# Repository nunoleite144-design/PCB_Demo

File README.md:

# PCB do Painel Solar 1U — ICARUS

Repositório de trabalho relativo ao desenho preliminar da PCB do painel solar 1U do projeto ICARUS, no âmbito da Porto Space Team.

Esta versão agrega o projeto KiCad, os footprints preliminares e a documentação técnica de apoio à revisão interna.

## Revisão atual

A revisão de trabalho actual é a **v0.7**:

- `hardware/ICARUS_1U_Solar_Panel_PCB_v0p7.kicad_sch`
- `hardware/ICARUS_1U_Solar_Panel_PCB_v0p7.kicad_pcb`
- `hardware/ICARUS_1U_Solar_Panel_PCB_v0p7.kicad_pro`

Esta revisão adopta **1S2P (duas células em paralelo)** como topologia base, **move o conector Molex `J1` para a face inferior (`B.Cu`)** conforme orientação do líder de equipa, mantém os test pads `PANEL_NEG` e `PANEL_POS`, e mantém `BENCH_ONLY_PANEL_NEG`/`BENCH_ONLY_PANEL_POS` apenas como fallback de bancada. O `D1` (TVS DNP) e o `TP2` (SERIES_MID) da v0.6 foram **removidos** porque deixam de ser necessários em paralelo.

Estado desta revisão: **pré-validação física**. Não está aprovada para fabrico final nem para voo.

A v0.6 (2S1P série) permanece em histórico Git como branch `v0.6-internal-review` e em `main` antes do merge da v0.7.

## Estado atual

A configuração elétrica de referência é **1S2P** com duas células solares **TJ3xSCA-4080 Tipo 32** por painel, ligadas em paralelo.

Parâmetros de referência usados no dimensionamento:

| Parâmetro | Valor |
|---|---:|
| `Voc_cell` | 2.70 V @ 25 °C |
| `Vmp_cell` | 2.37 V @ 25 °C |
| `Jm` | 17.9 mA/cm² |
| Área ativa | 30.18 cm² |
| `dVoc/dT` | −6.0 mV/°C por célula |

Valores calculados para o painel 1S2P:

| Grandeza | Valor |
|---|---:|
| `Voc_panel` @ 25 °C BOL | 2.70 V |
| `Vmp_panel` @ 25 °C | 2.37 V |
| `Isc` @ 25 °C | ≈ 1.12 A |
| `Imp` @ 25 °C | ≈ 1.08 A |
| `Pmp` @ 25 °C | ≈ 2.65 W |

Ligação elétrica final (1S2P):

| Nó | Ligação |
|---|---|
| `SC1_NEG` (tabs/frente) | `PANEL_NEG` |
| `SC1_POS` (centro/verso) | `PANEL_POS` |
| `SC2_NEG` (tabs/frente) | `PANEL_NEG` |
| `SC2_POS` (centro/verso) | `PANEL_POS` |

Não existe net intermédia (`SERIES_MID` foi removida na transição 2S1P → 1S2P).

## Interface EPS I

O EPS usado é o **EnduroSat EPS I**. O pinout solar que deve ser respeitado no cabo/PCB é (Tabela 8 do EPS I User Manual):

| Pino do conector solar EPS I | Função |
|---:|---|
| 1 | PV− / negativo |
| 2 | PV− / negativo |
| 3 | PV+ / positivo |
| 4 | PV+ / positivo |

`J1` está montado em `B.Cu` (parte inferior da PCB) por instrução do líder de equipa, mantendo o pinout acima.

Limites relevantes por canal solar (Tabela 12 do EPS I User Manual):

| Limite | Valor | Notas |
|---|---:|---|
| Tensão mínima de entrada (boost UVLO) | ≈ 0.78 V | `VF_blocking_diode + 0.5 V` |
| Tensão típica de operação | 4.66 V | Ponto referenciado pelo EPS |
| Tensão máxima — OVP trigger | 5.5 V | EPS tem OVP **integrada** acima deste valor |
| Corrente máxima de entrada | 1.8 A | — |

A PCB e o harness devem ser verificados por continuidade antes de qualquer ligação ao EPS.

## Margens eléctricas (1S2P)

A transição para paralelo **elimina** o risco de sobretensão a frio que dominava a v0.6:

| Cenário | Valor 1S2P | vs limite 5.5 V (OVP trigger) |
|---|---:|---|
| `Voc_panel` @ 25 °C BOL | 2.70 V | margem 2.80 V |
| `Voc_panel` @ −40 °C BOL | 2.94 V | margem 2.56 V |
| `Voc_panel` @ −80 °C BOL (extremo) | 3.33 V | margem 2.17 V |

`Vmp` opera abaixo do ponto típico do EPS (2.37 V vs 4.66 V); o boost MPPT trabalha com rácio mais alto, com ligeira perda de eficiência mas funcionalmente correcto. UVLO ≈ 0.78 V está confortavelmente abaixo de `Vmp`.

Ver `docs/VALIDACAO_TOPOLOGIA_PARALELO_v0p7.md` para a análise completa.

## Conteúdo do repositório

- `hardware/` — projeto KiCad da PCB (esquemático, PCB, projeto), símbolos `ICARUS.kicad_sym`, footprints (`footprints/ICARUS_Solar.pretty`, `footprints/ICARUS_Connector.pretty`) e tabelas de bibliotecas.
- `docs/VALIDACAO_TOPOLOGIA_PARALELO_v0p7.md` — **documento de referência da v0.7**: justificação técnica, mapa de pads, mudanças aplicadas, estado dos relatórios.
- `docs/VALIDACAO_DATASHEETS_v0p6.md` — cruzamento do design com os datasheets oficiais (célula e EPS I); inclui actualização v0.7 sobre a OVP integrada.
- `docs/ANALISE_TERMICA_VOC_v0p6.md` — análise térmica de sobretensão (histórica, **superseded** pela mudança para 1S2P).
- `docs/DECISAO_TVS_v0p7.md` — decisão de clamp TVS (histórica, **superseded** — `D1` foi removido).
- `docs/CORRECAO_TOPOLOGIA_SERIE_v0p6.md` — correcção da anti-série da v0.6 (histórica).
- `docs/REVIEW_ACTIONS_v0p6.md` — resumo das ações da v0.6 (histórico).
- `docs/VALIDACAO_LOCAL_v0p6.md` — estado dos relatórios ERC/DRC da v0.6 (histórico).
- `docs/MECHANICAL_CELL_CLEARANCE_v0p6.md` — folga mecânica nominal entre células (continua válido em v0.7).
- `docs/CELL_UNDER_COPPER_RISK_v0p6.md` — auditoria de cobre sob as células da v0.6 (histórico parcial).
- `reports/` — relatórios ERC/DRC e plots SVG (top/bottom/fab) das revisões v0.6 e v0.7.
- `test_logs/LIBRARY_WARNINGS_WAIVER_v0p6.md` — waiver técnico dos warnings de biblioteca do ERC/DRC.
- `TJ30SCA-4080V4.pdf` — datasheet da célula solar TJ3xSCA-4080.
- `EPS_I_User_Manual.pdf` — manual do EnduroSat EPS I (limites de entrada solar e pinout do conector).

## Regra de fecho

Não considerar o desenho **flight-ready** nem **fabrication-ready** sem:

- ERC/DRC oficial no KiCad GUI (CLI já corrido e limpo);
- desenho de montagem CIC da AzurSpace (geometria das tabs e contacto de verso);
- drawing oficial do Molex 53398-0471 para validar footprint final;
- validação mecânica com estrutura e células reais;
- validação do harness por continuidade;
- testes elétricos com carga antes de ligação ao EPS;
- revisão por pelo menos uma segunda pessoa.

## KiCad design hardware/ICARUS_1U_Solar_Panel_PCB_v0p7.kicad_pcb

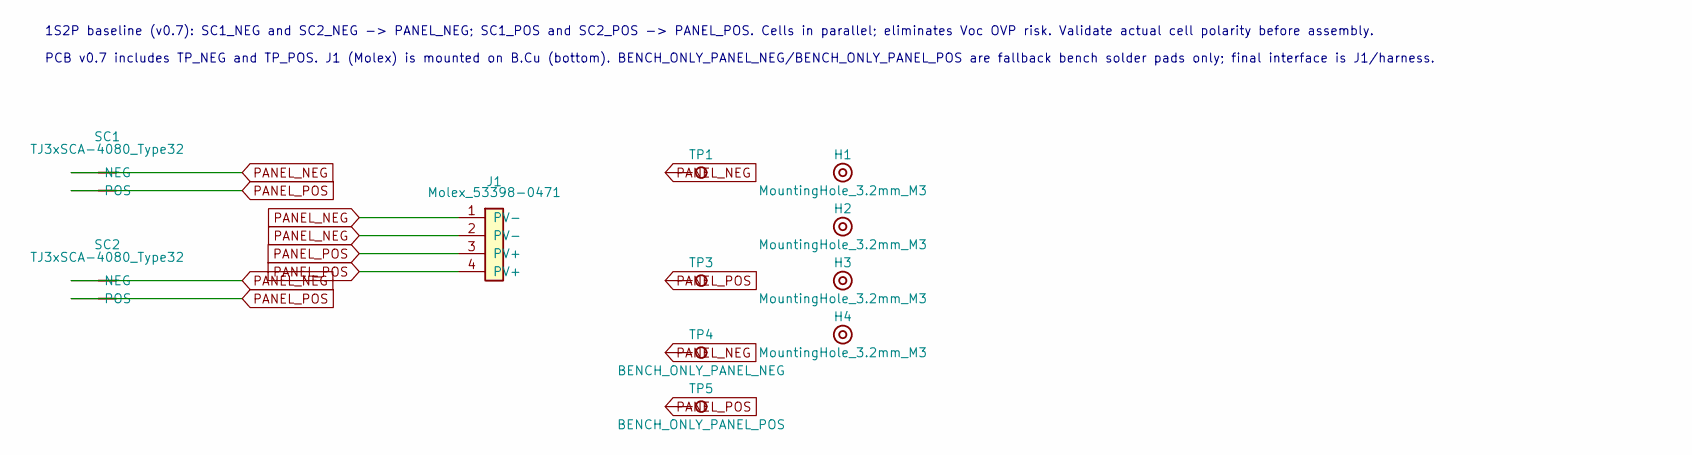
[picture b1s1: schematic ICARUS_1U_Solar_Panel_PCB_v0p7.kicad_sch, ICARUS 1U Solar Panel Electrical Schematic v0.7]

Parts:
H1, H2, H3, H4: MountingHole_3.2mm_M3
J1: Molex_53398-0471; Molex_53398-0471_1x04_P1.25mm_PRELIMINARY
SC1, SC2: TJ3xSCA-4080_Type32; TJ3xSCA_4080_CIC
TP1: PANEL_NEG; TestPoint_Pad_D2.0mm
TP3: PANEL_POS; TestPoint_Pad_D2.0mm
TP4: BENCH_ONLY_PANEL_NEG; TestPoint_Pad_D2.5mm
TP5: BENCH_ONLY_PANEL_POS; TestPoint_Pad_D2.5mm

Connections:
PANEL_NEG: J1.1 (PV-), J1.2 (PV-), SC1.1 (NEG), SC2.1 (NEG), TP1.1, TP4.1
PANEL_POS: J1.3 (PV+), J1.4 (PV+), SC1.2 (POS), SC2.2 (POS), TP3.1, TP5.1

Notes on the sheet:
1S2P baseline (v0.7): SC1_NEG and SC2_NEG -> PANEL_NEG; SC1_POS and SC2_POS -> PANEL_POS. Cells in parallel; eliminates Voc OVP risk. Validate actual cell polarity before assembly.
PCB v0.7 includes TP_NEG and TP_POS. J1 (Molex) is mounted on B.Cu (bottom). BENCH_ONLY_PANEL_NEG/BENCH_ONLY_PANEL_POS are fallback bench solder pads only; final interface is J1/harness.

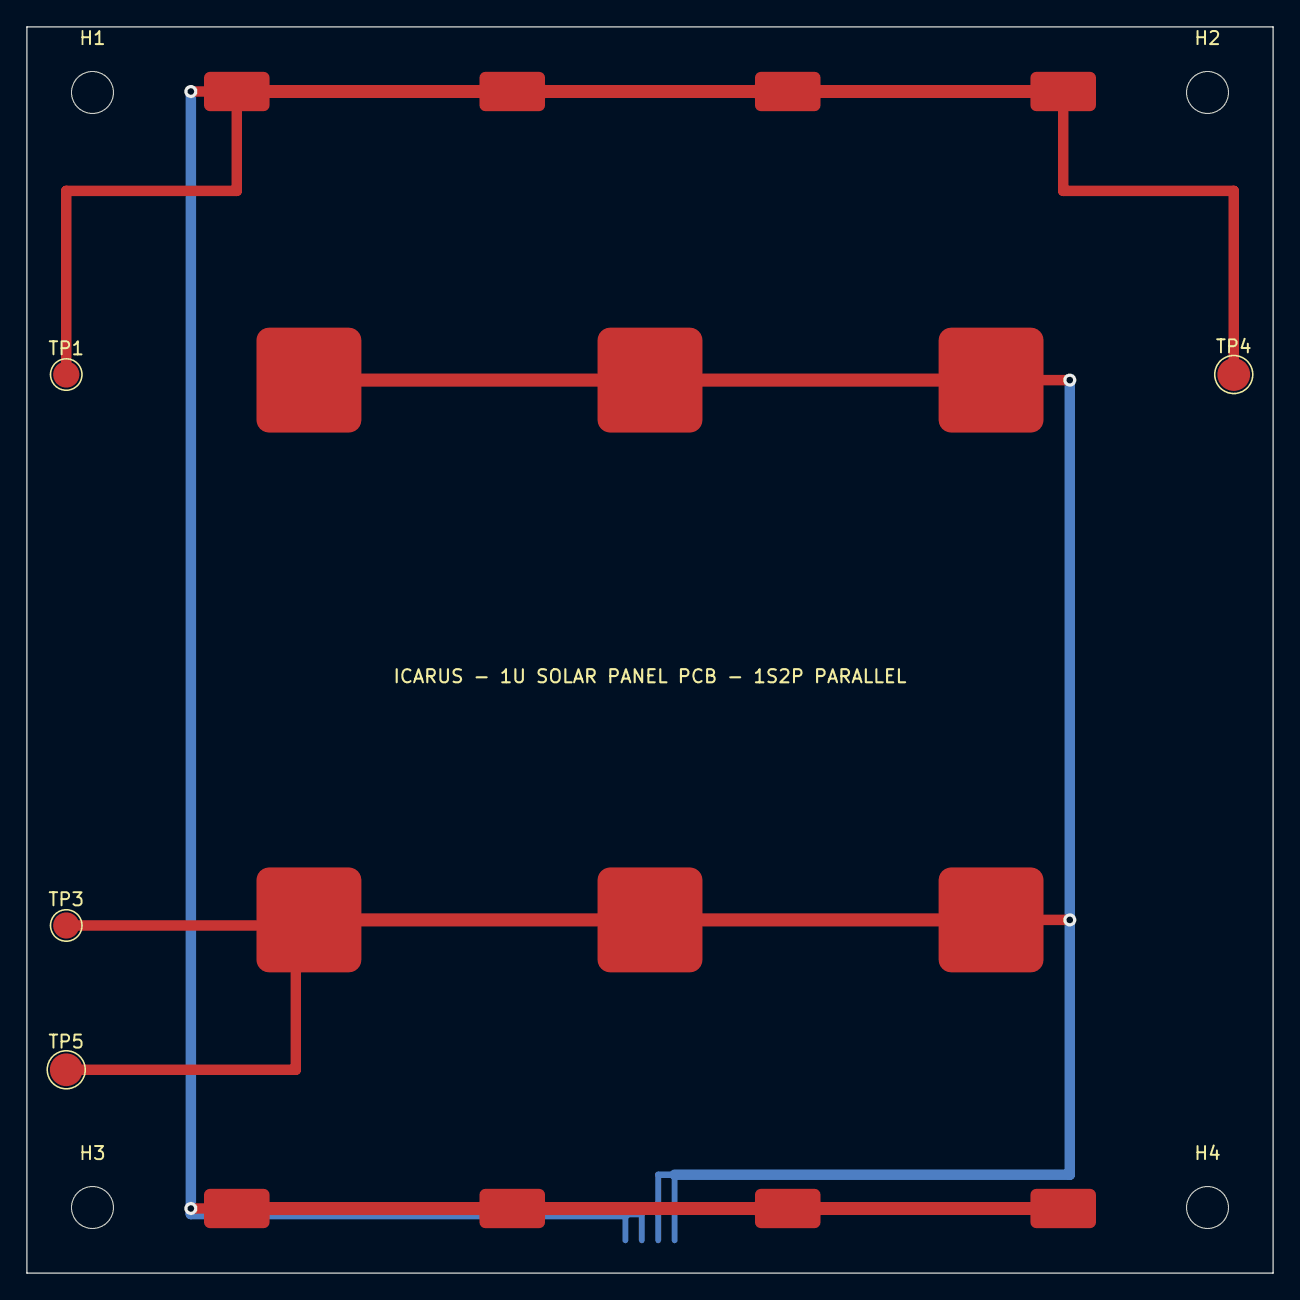
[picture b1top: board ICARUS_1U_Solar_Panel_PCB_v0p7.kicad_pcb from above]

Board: 2 copper layers, 95.0 x 95.0 mm, 11 parts (1 on the bottom side), 2 nets.

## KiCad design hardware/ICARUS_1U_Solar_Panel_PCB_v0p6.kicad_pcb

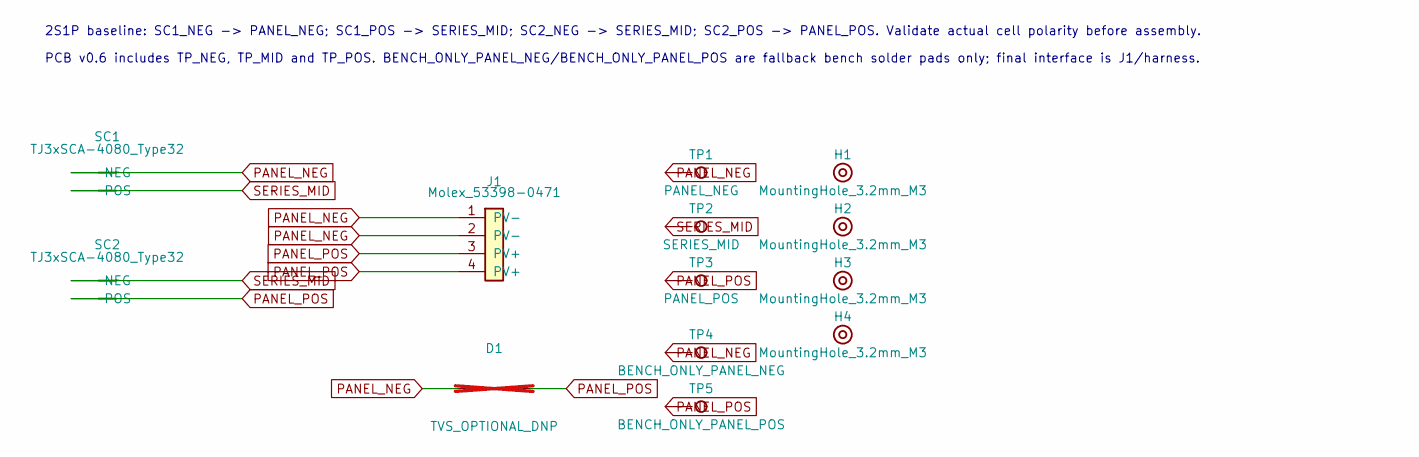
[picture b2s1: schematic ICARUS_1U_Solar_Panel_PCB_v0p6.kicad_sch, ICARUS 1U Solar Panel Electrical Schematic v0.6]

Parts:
D1: TVS_OPTIONAL_DNP; D_SOD-123; not fitted
H1, H2, H3, H4: MountingHole_3.2mm_M3
J1: Molex_53398-0471; Molex_53398-0471_1x04_P1.25mm_PRELIMINARY
SC1, SC2: TJ3xSCA-4080_Type32; TJ3xSCA_4080_CIC
TP1: PANEL_NEG; TestPoint_Pad_D2.0mm
TP2: SERIES_MID; TestPoint_Pad_D2.0mm
TP3: PANEL_POS; TestPoint_Pad_D2.0mm
TP4: BENCH_ONLY_PANEL_NEG; TestPoint_Pad_D2.5mm
TP5: BENCH_ONLY_PANEL_POS; TestPoint_Pad_D2.5mm

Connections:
PANEL_NEG: D1.1 (A), J1.1 (PV-), J1.2 (PV-), SC1.1 (NEG), TP1.1, TP4.1
PANEL_POS: D1.2 (K), J1.3 (PV+), J1.4 (PV+), SC2.2 (POS), TP3.1, TP5.1
SERIES_MID: SC1.2 (POS), SC2.1 (NEG), TP2.1

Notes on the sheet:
2S1P baseline: SC1_NEG -> PANEL_NEG; SC1_POS -> SERIES_MID; SC2_NEG -> SERIES_MID; SC2_POS -> PANEL_POS. Validate actual cell polarity before assembly.
PCB v0.6 includes TP_NEG, TP_MID and TP_POS. BENCH_ONLY_PANEL_NEG/BENCH_ONLY_PANEL_POS are fallback bench solder pads only; final interface is J1/harness.

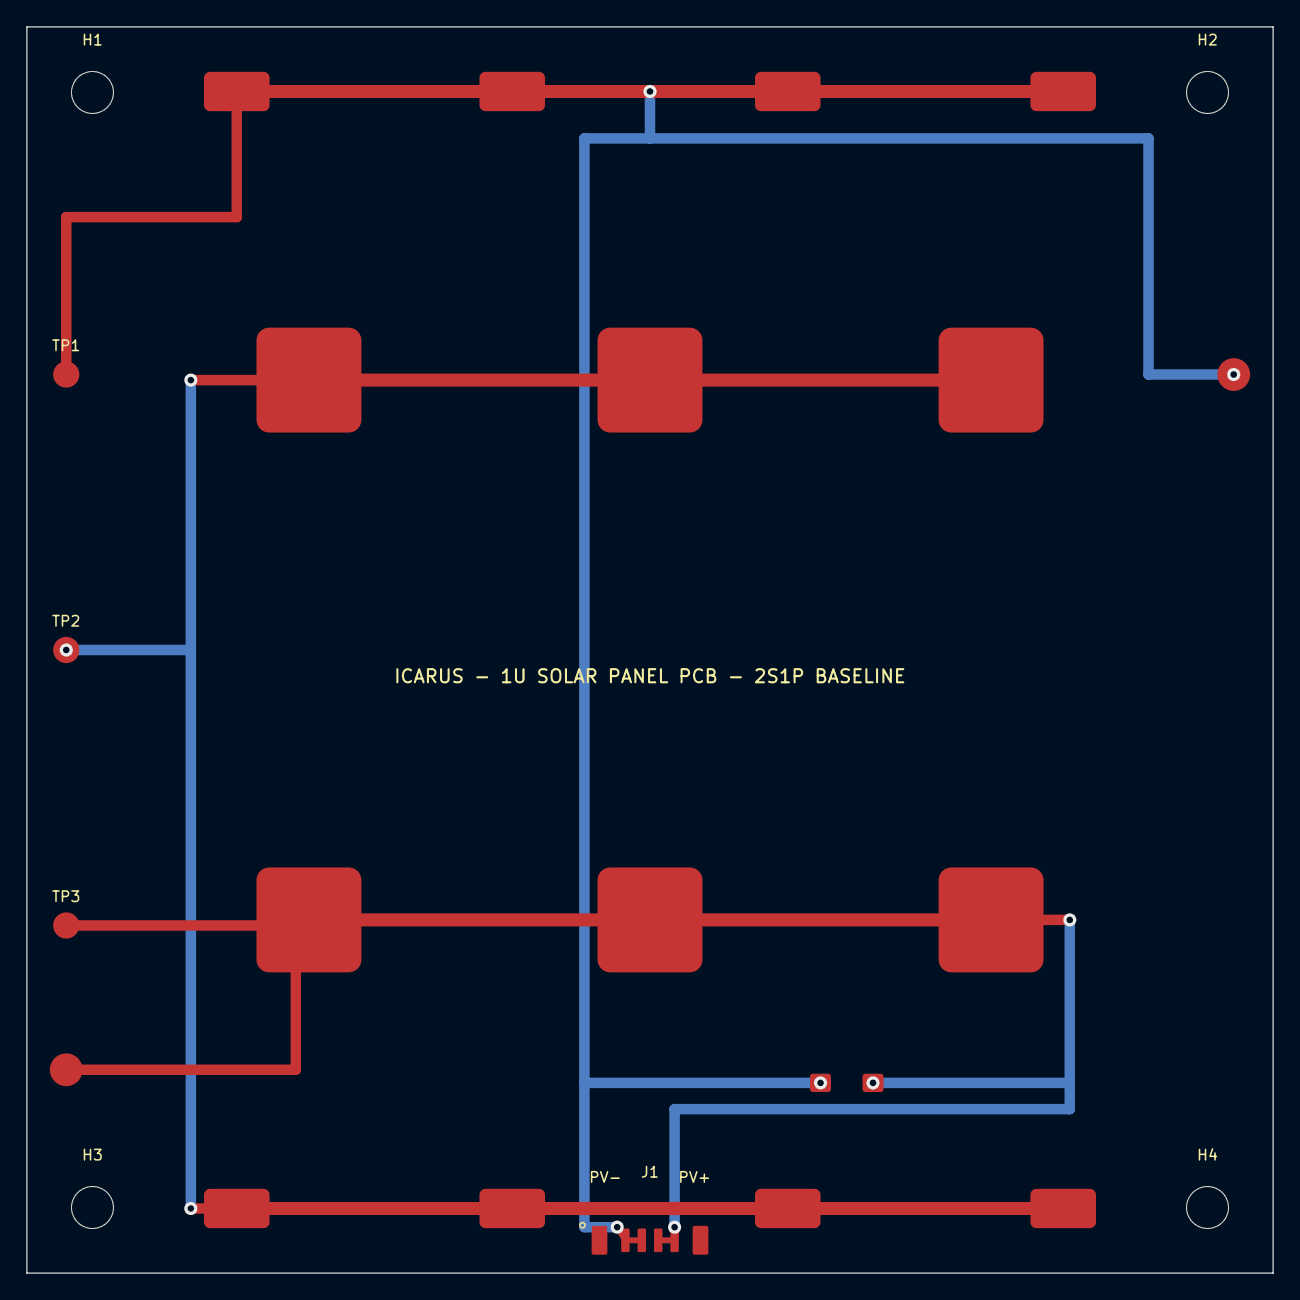
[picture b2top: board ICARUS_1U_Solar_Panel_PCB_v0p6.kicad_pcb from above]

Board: 2 copper layers, 95.0 x 95.0 mm, 13 parts (0 on the bottom side), 3 nets.

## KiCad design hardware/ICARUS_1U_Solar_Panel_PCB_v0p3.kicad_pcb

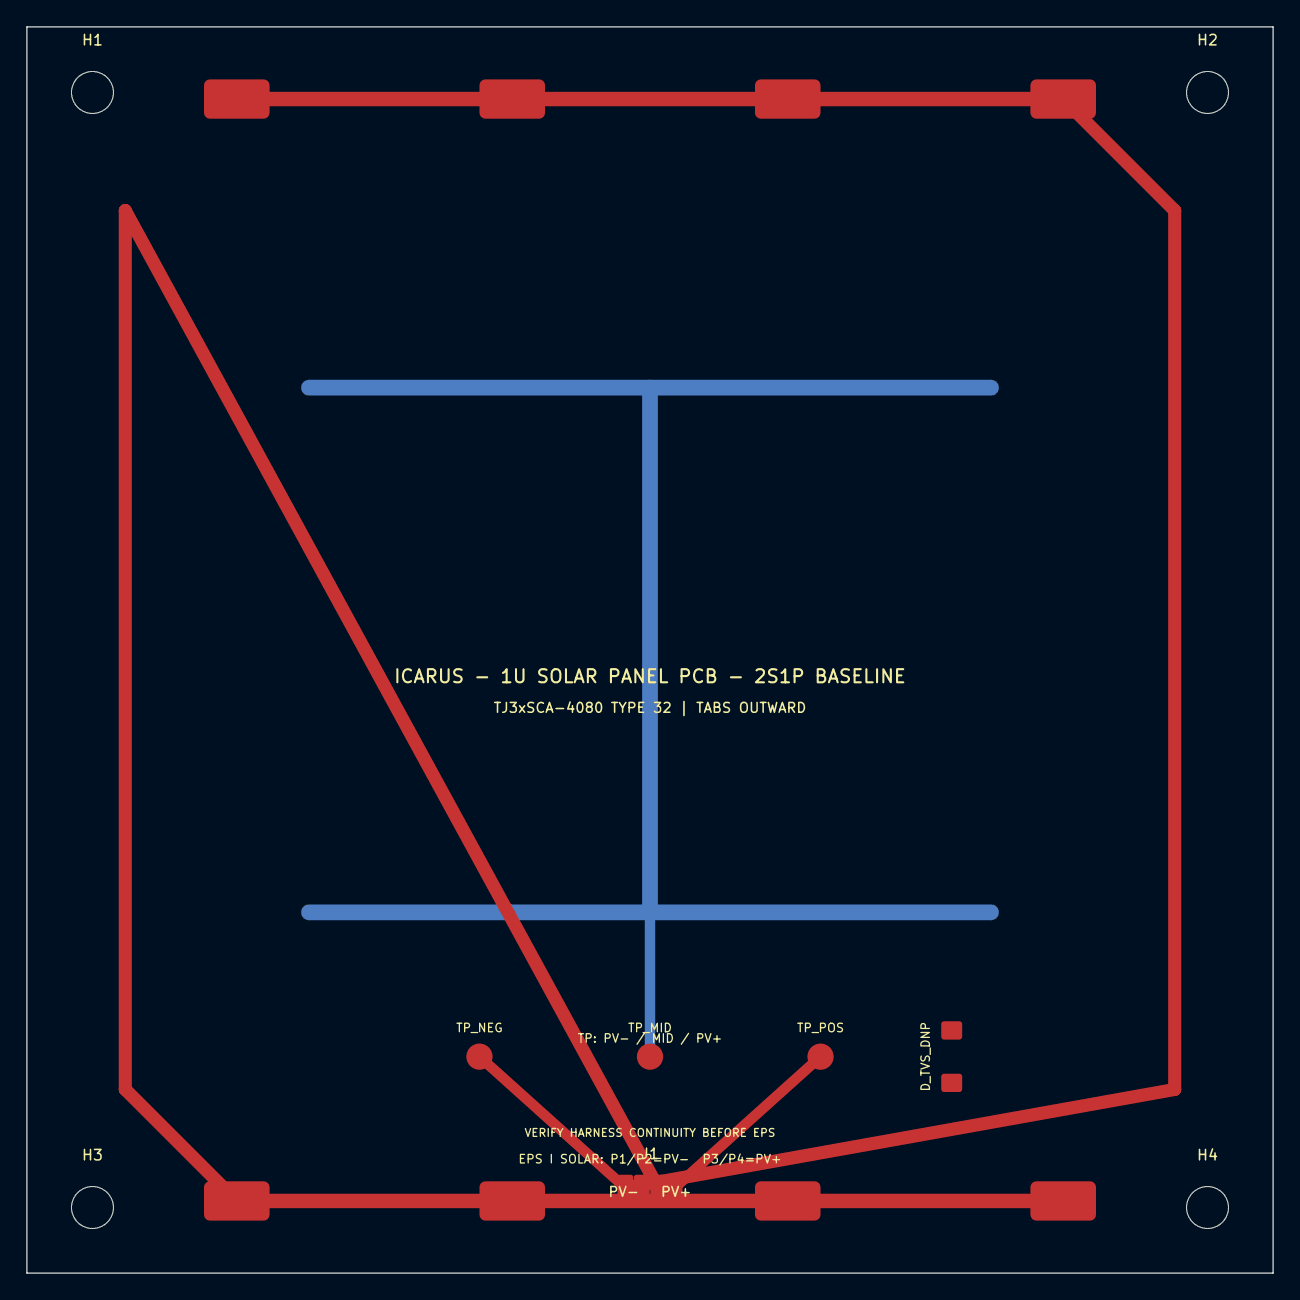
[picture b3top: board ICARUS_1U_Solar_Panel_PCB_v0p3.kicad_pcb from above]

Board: 2 copper layers, 95.0 x 95.0 mm, 11 parts (0 on the bottom side), 3 nets.

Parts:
D_TVS_DNP: TVS_OPTIONAL_DNP; D_SOD-123
H1, H2, H3, H4: MountingHole_3.2mm_M3
J1: EPS_SOLAR_OUT_4P_PLACEHOLDER; SOLAR_OUT_4P_1p25_PLACEHOLDER
SC1, SC2: TJ3xSCA-4080 CIC; TJ3xSCA_4080_CIC
TP_MID: SERIES_MID; TestPoint_Pad_D2.0mm
TP_NEG: PANEL_NEG; TestPoint_Pad_D2.0mm
TP_POS: PANEL_POS; TestPoint_Pad_D2.0mm

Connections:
PANEL_NEG: D_TVS_DNP.1, J1.1, J1.2, SC1.N1, SC1.N2, SC1.N3, SC1.N4, TP_NEG.1
PANEL_POS: D_TVS_DNP.2, J1.3, J1.4, SC2.N1, SC2.N2, SC2.N3, SC2.N4, TP_POS.1
SERIES_MID: SC1.P1, SC1.P2, SC1.P3, SC2.P1, SC2.P2, SC2.P3, TP_MID.1

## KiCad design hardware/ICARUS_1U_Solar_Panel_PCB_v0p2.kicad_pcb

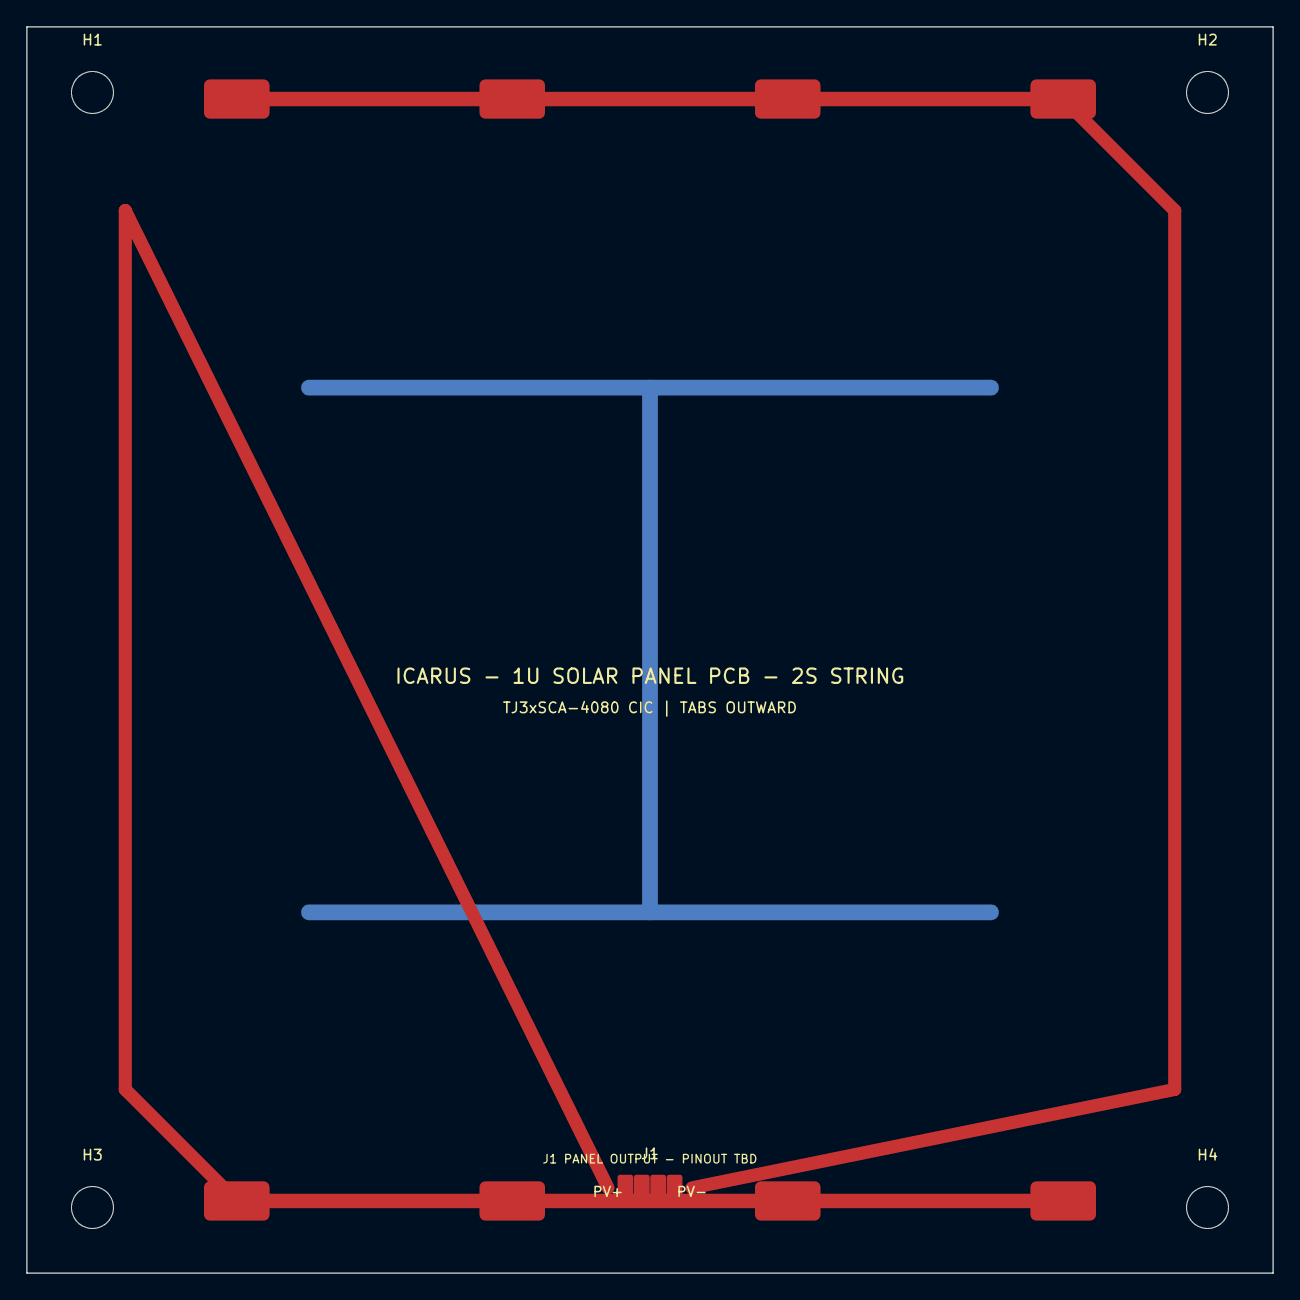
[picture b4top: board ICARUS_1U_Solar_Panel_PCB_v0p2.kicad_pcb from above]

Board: 2 copper layers, 95.0 x 95.0 mm, 7 parts (0 on the bottom side), 3 nets.

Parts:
H1, H2, H3, H4: MountingHole_3.2mm_M3
J1: SOLAR_OUT_4P_1p25_PLACEHOLDER
SC1, SC2: TJ3xSCA-4080 CIC; TJ3xSCA_4080_CIC

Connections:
PANEL_NEG: J1.3, J1.4, SC1.N1, SC1.N2, SC1.N3, SC1.N4
PANEL_POS: J1.1, J1.2, SC2.N1, SC2.N2, SC2.N3, SC2.N4
SERIES_MID: SC1.P1, SC1.P2, SC1.P3, SC2.P1, SC2.P2, SC2.P3

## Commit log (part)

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2026-05-16 Initialize repository with ICARUS PCB design-review README
2026-05-16 Add ICARUS v0.2 KiCad PCB design-review board
2026-05-16 Add ICARUS v0.2 KiCad project file
2026-05-16 Add review footprint for TJ3xSCA-4080 CIC solar cell
2026-05-16 Add panel-output connector placeholder footprint
2026-05-16 Add ICARUS PCB design review notes
2026-05-16 Substituir README por versão revista em português técnico
2026-05-16 Adicionar README técnico em português
2026-05-16 Ajustar redação do README
2026-05-16 Adicionar ficheiro de teste
2026-05-16 Expandir README
2026-05-16 Acrescentar secção de conteúdo
2026-05-16 Ajustar secção de conteúdo do README
2026-05-16 Adicionar notas de revisão técnica em português
2026-05-16 Traduzir notas técnicas para português de Portugal
2026-05-16 Remover ficheiro temporário
2026-05-16 Rever footprint provisório do conector
2026-05-16 Rever footprint preliminar da célula
2026-05-16 Restaurar conteúdo técnico do README
2026-05-23 Document ICARUS solar panel electrical baseline and EPS pinout
2026-05-23 Add ICARUS solar panel electrical baseline document
2026-05-23 Add harness pinout and continuity procedure
2026-05-23 Add solar cell arrival bench test plan
2026-05-23 Add v0.3 release readiness checklist
2026-05-23 Add v0.3 KiCad PCB with corrected EPS pinout and test pads
2026-05-23 Add v0.4 KiCad schematic for ERC
2026-05-23 Add preliminary Molex 53398-0471 footprint for v0.4 validation
2026-05-23 Fix v0.4 schematic annotation by using numeric TVS reference
2026-05-28 Remove PR_BODY_v0p6.md (already deleted, finalize)
